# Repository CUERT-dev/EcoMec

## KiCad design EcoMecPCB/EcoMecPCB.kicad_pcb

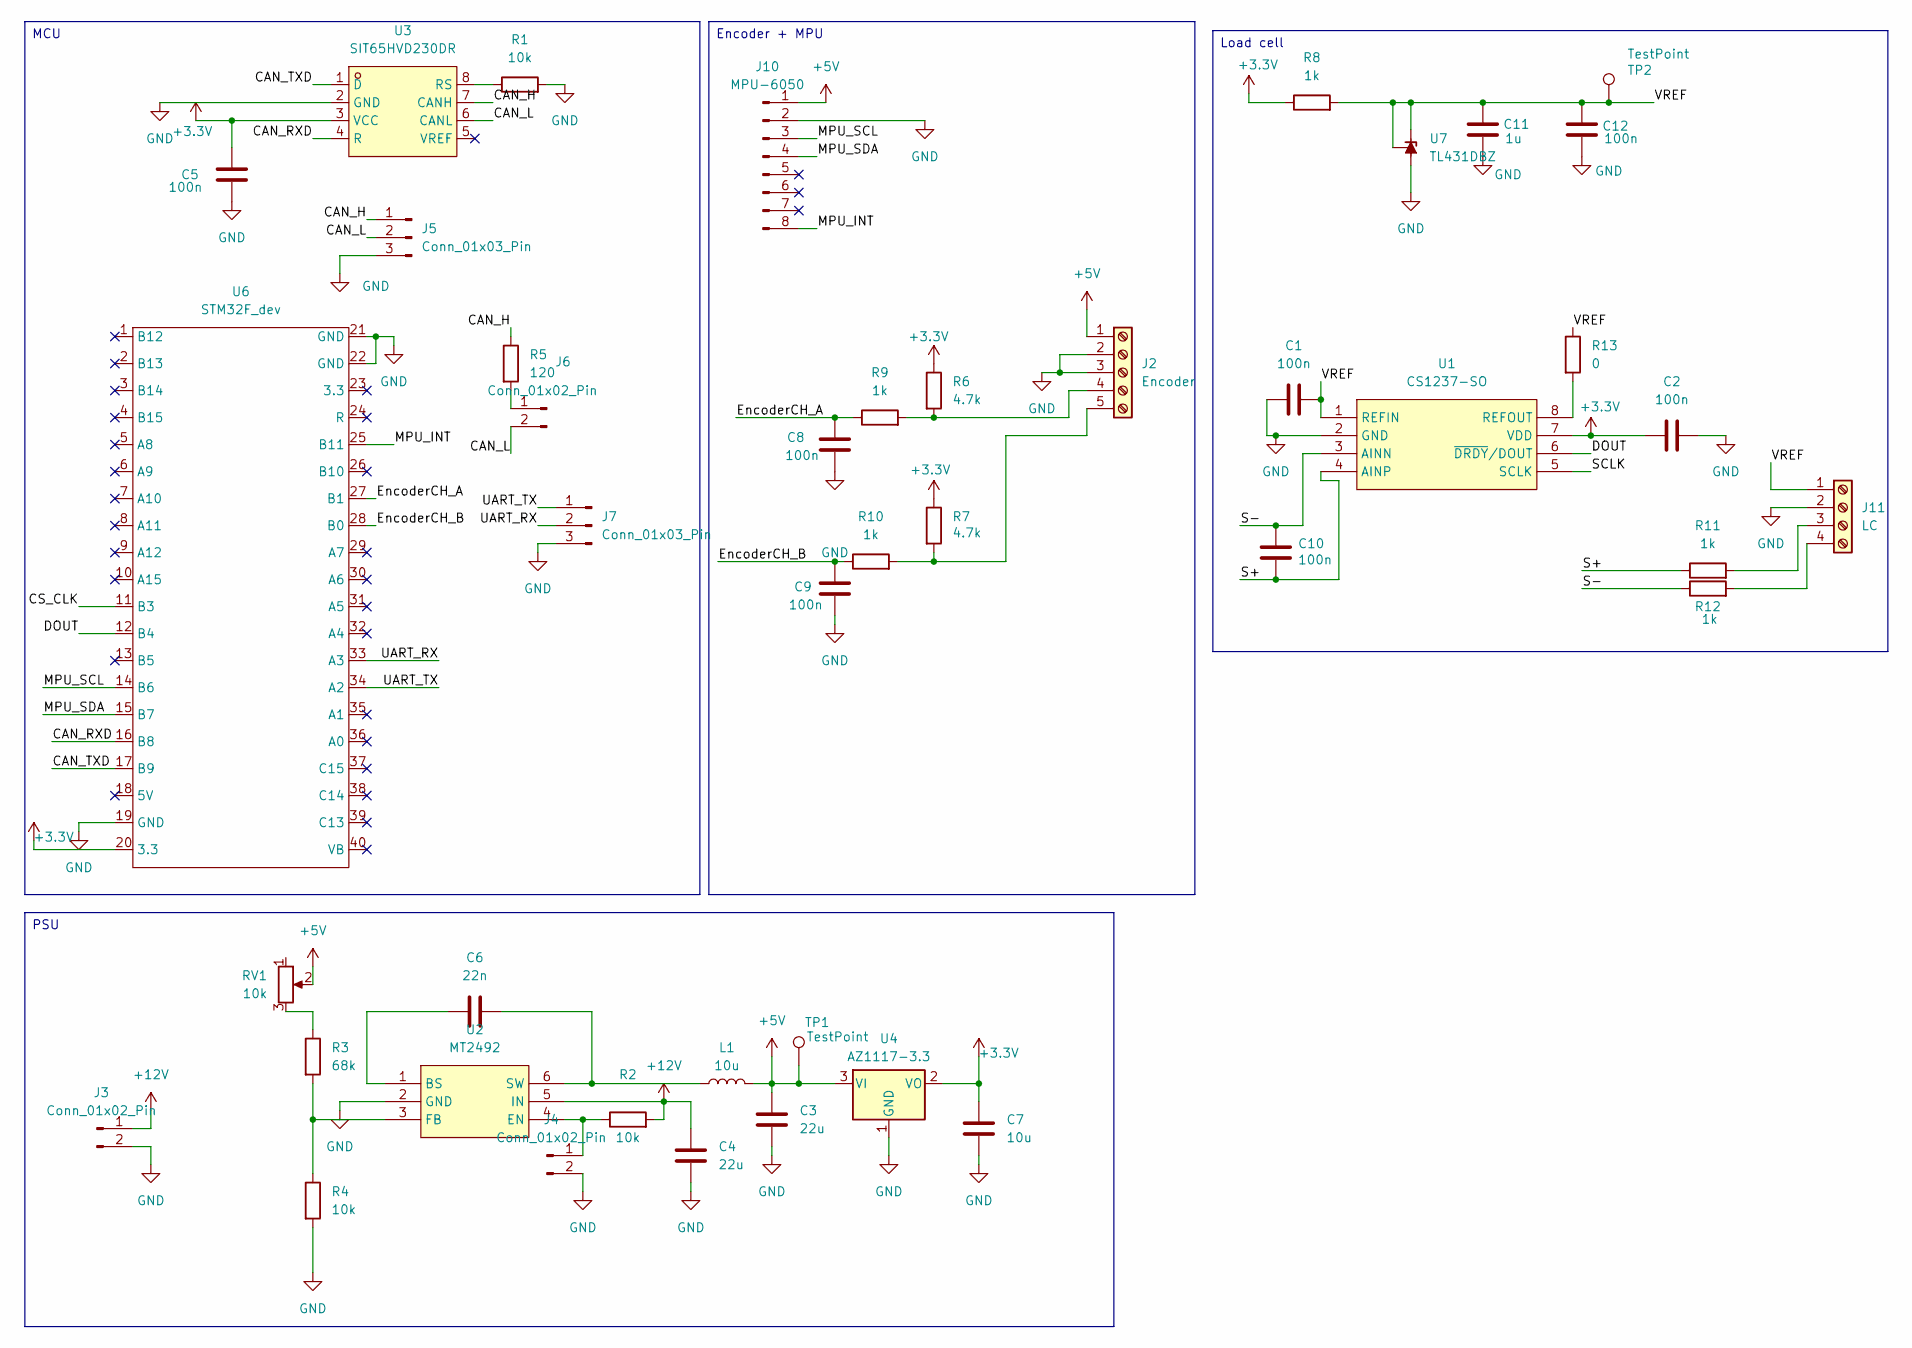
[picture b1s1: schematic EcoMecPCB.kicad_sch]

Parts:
C1, C2, C5, C8, C9, C10, C12: 100n; C_1206_3216Metric_Pad1.33x1.80mm_HandSolder
C3, C4: 22u; C_1206_3216Metric_Pad1.33x1.80mm_HandSolder
C6: 22n; C_1206_3216Metric_Pad1.33x1.80mm_HandSolder
C7: 10u; C_1206_3216Metric_Pad1.33x1.80mm_HandSolder
C11: 1u; C_1206_3216Metric_Pad1.33x1.80mm_HandSolder
J2: Encoder; TerminalBlock_Phoenix_PT-1,5-5-3.5-H_1x05_P3.50mm_Horizontal
J3: Conn_01x02_Pin; JST_XH_B2B-XH-A_1x02_P2.50mm_Vertical
J4, J6: Conn_01x02_Pin; PinHeader_1x02_P2.54mm_Vertical
J5, J7: Conn_01x03_Pin; JST_XH_B3B-XH-A_1x03_P2.50mm_Vertical
J10: MPU-6050; PinHeader_1x08_P2.54mm_Vertical
J11: LC; TerminalBlock_Phoenix_PT-1,5-4-3.5-H_1x04_P3.50mm_Horizontal
L1: 10u; IND-SMD_L7.2-W6.6_GPSR07X0
R1, R2, R4: 10k; R_1206_3216Metric_Pad1.30x1.75mm_HandSolder
R3: 68k; R_1206_3216Metric_Pad1.30x1.75mm_HandSolder
R5: 120; R_1206_3216Metric_Pad1.30x1.75mm_HandSolder
R6, R7: 4.7k; R_1206_3216Metric_Pad1.30x1.75mm_HandSolder
R8, R9, R10, R11, R12: 1k; R_1206_3216Metric_Pad1.30x1.75mm_HandSolder
R13: 0; R_1206_3216Metric_Pad1.30x1.75mm_HandSolder
RV1: 10k; Potentiometer_Bourns_3296W_Vertical
TP1, TP2: TestPoint; TestPoint_Pad_D1.5mm
U1: CS1237-SO; SOIC-8_L5.0-W4.0-P1.27-LS6.0-BL; LCSC Part C77801
U2: MT2492; SOT-23-6_L2.9-W1.6-P0.95-LS2.8-BL_3; LCSC Part C89358
U3: SIT65HVD230DR; SOP-8_L4.9-W3.9-P1.27-LS6.0-BL; LCSC Part C496619
U4: AZ1117-3.3; SOT-89-3_Handsoldering
U6: STM32F_dev; STM32F_devboard
U7: TL431DBZ; SOT-23

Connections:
+3.3V: C2.1, C5.2, C7.1, R6.1, R7.1, R8.1, U1.7 (VDD), U3.3 (VCC), U4.2 (VO), U6.20 (3.3)
+5V: C3.2, J2.1, J10.1, L1.2, RV1.2, TP1.1, U4.3 (VI)
+12V: C4.1, J3.1, R2.2, U2.5 (IN)
/CAN_H: J5.1, R5.1, U3.7 (CANH)
/CAN_L: J5.2, J6.2, U3.6 (CANL)
/CAN_RXD: U3.4 (R), U6.16 (B8)
/CAN_TXD: U3.1 (D), U6.17 (B9)
/CS_CLK: U6.11 (B3)
/DOUT: U1.6 (~DRDY/DOUT), U6.12 (B4)
/EncoderCH_A: C8.2, R9.1, U6.27 (B1)
/EncoderCH_B: C9.2, R10.1, U6.28 (B0)
/MPU_INT: J10.8, U6.25 (B11)
/MPU_SCL: J10.3, U6.14 (B6)
/MPU_SDA: J10.4, U6.15 (B7)
/S+: C10.1, R11.1, U1.4 (AINP)
/S-: C10.2, R12.1, U1.3 (AINN)
/SCLK: U1.5 (SCLK)
/UART_RX: J7.2, U6.33 (A3)
/UART_TX: J7.1, U6.34 (A2)
/VREF: C1.2, C11.2, C12.2, J11.1, R8.2, R13.1, TP2.1, U1.1 (REFIN), U7.1 (K), U7.2 (REF)
GND: C1.1, C2.2, C3.1, C4.2, C5.1, C7.2, C8.1, C9.1, C11.1, C12.1, J2.2, J2.3, J3.2, J4.2, J5.3, J7.3, J10.2, J11.2, R1.2, R4.2, U1.2 (GND), U2.2 (GND), U3.2 (GND), U4.1 (GND), U6.19 (GND), U6.21 (GND), U6.22 (GND), U7.3 (A)
unnamed: J2.4, R6.2, R9.2
unnamed: J2.5, R7.2, R10.2
unnamed: J4.1, R2.1, U2.4 (EN)
unnamed: J6.1, R5.2
unnamed: J11.3, R11.2
unnamed: J11.4, R12.2
unnamed: R3.1, RV1.3
unnamed: R13.2, U1.8 (REFOUT)
unnamed: C6.1, U2.1 (BS)
unnamed: R3.2, R4.1, U2.3 (FB)
unnamed: C6.2, L1.1, U2.6 (SW)
unnamed: R1.1, U3.8 (RS)

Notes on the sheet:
PSU
Encoder + MPU
Load cell
MCU

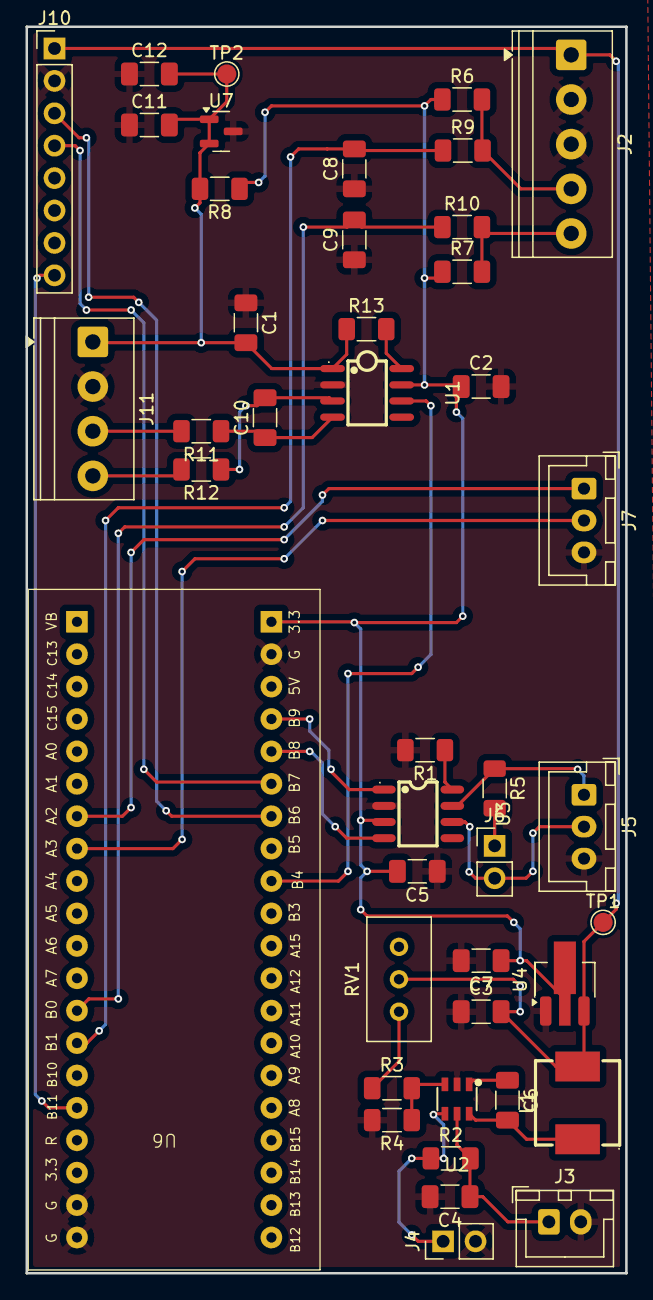
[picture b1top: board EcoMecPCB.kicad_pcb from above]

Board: 2 copper layers, 47.0 x 97.7 mm, 43 parts (0 on the bottom side), 31 nets.

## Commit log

2026-03-05 fadel el encoder w I2C pins for CS1237
    fadel el encoder w I2C pins for CS1237
2026-03-06 Pin layout done
    Pin layout done
2026-03-06 Schematic done
    Schematic done
2026-03-06 Schematic inshallah Done
    Schematic inshallah Done
2026-03-14 Finished routing and layout
    finished layout
    finished routing
